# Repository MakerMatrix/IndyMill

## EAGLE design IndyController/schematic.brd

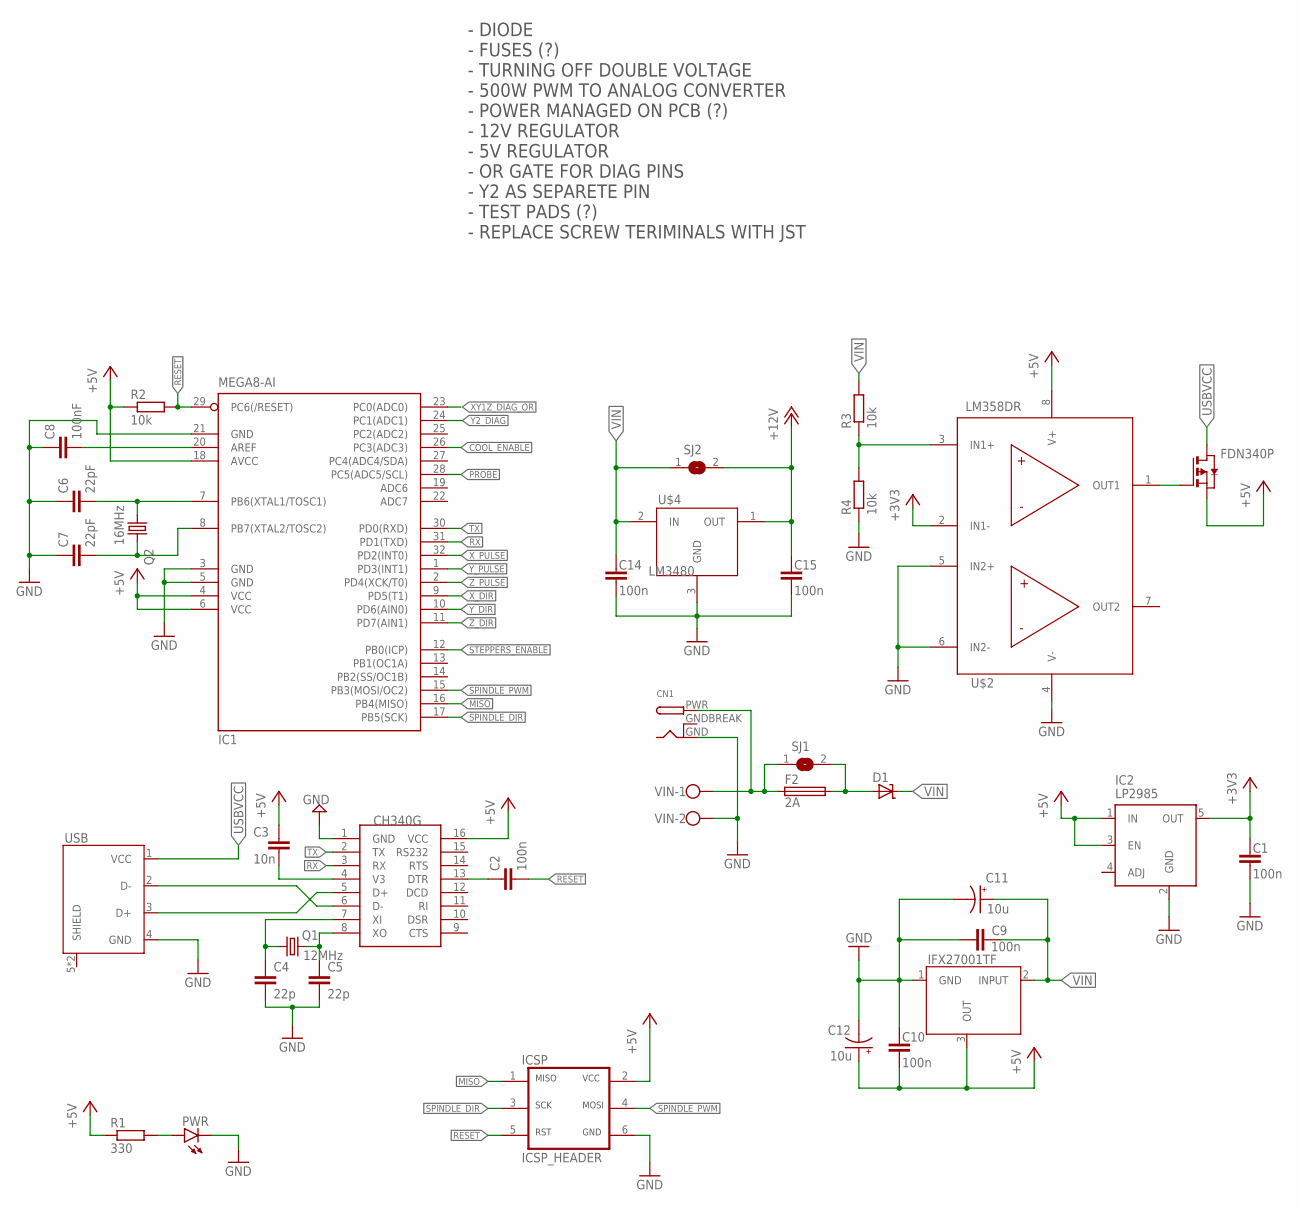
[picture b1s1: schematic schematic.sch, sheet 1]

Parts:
C1, C2, C9, C10, C14, C15: 100n; C0603
C3: 10n; C0603
C4, C5: 22p; C0603
C6, C7: 22pF; C0603
C8: 100nF; C0603
C11, C12: 10u; E5-5
CN1: DCBARRELPTH; DCJACK_2MM_PTH
D1: SD-SMA; SMA
F2: 2A; GSH15
FDN340P: FDN340PSOT23; SOT95P240X110-3N
IC1: MEGA8-AI; TQFP32-08
IC2: LP2985; SOT23-5
IFX27001TF: IFX27001TFV50TO252; TO228P998X230-3N
PWR: LEDCHIPLED_0805; CHIPLED_0805
Q1: 12MHz; 5.0X3.2_2
Q2: 16MHz; 5.0X3.2_2
R1: 330; R0603
R2, R3, R4: 10k; R0603
SJ1: SJW
SJ2: SJ
U$1: CH340G; SOIC16
U$2: LM358; SOIC127P599X175-8N
U$4: LM3480; SOT95P247X112-3N
U$6: ICSP_HEADER
USB: U-USBBR04P-F000
VIN: W237-102

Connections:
+3V3: C1.2, IC2.5 (OUT), U$2.2 (IN1-)
+5V: C3.1, C10.1, C12.+, FDN340P.2 (S), IC1.4 (VCC), IC1.6 (VCC), IC1.18 (AVCC), IC2.1 (IN), IC2.3 (EN), IFX27001TF.3 (OUT), R1.1, R2.1, U$1.16 (VCC), U$2.8 (V+), U$6.2 (VCC); also elsewhere on the board
+12V: C15.2, SJ2.2, U$4.1 (OUT); also elsewhere on the board
COOL_ENABLE: IC1.26 (PC3(ADC3)); also elsewhere on the board
GND: C1.1, C4.2, C5.2, C6.1, C7.1, C8.1, C9.1, C10.2, C11.-, C12.-, C14.1, C15.1, CN1.GND, IC1.3 (GND), IC1.5 (GND), IC1.21 (GND), IC2.2 (GND), IFX27001TF.1 (GND), PWR.C, R4.1, U$1.1 (GND), U$2.4 (V-), U$2.5 (IN2+), U$2.6 (IN2-), U$4.3 (GND), U$6.6 (GND), USB.4 (GND), VIN.2; also elsewhere on the board
GNDBREAK: CN1.GNDBREAK
MISO: IC1.16 (PB4(MISO)), U$6.1 (MISO)
unnamed: C3.2, U$1.4 (V3)
unnamed: C2.1, U$1.13 (DTR)
unnamed: C5.1, Q1.2, U$1.8 (XO)
unnamed: C4.1, Q1.1, U$1.7 (XI)
unnamed: U$1.6 (D-), USB.2 (D-)
unnamed: PWR.A, R1.2
unnamed: C6.2, IC1.7 (PB6(XTAL1/TOSC1)), Q2.1
unnamed: C7.2, IC1.8 (PB7(XTAL2/TOSC2)), Q2.2
unnamed: C8.2, IC1.20 (AREF)
unnamed: U$1.5 (D+), USB.3 (D+)
unnamed: FDN340P.1 (G), U$2.1 (OUT1)
unnamed: CN1.PWR, F2.1, SJ1.1, VIN.1
unnamed: R3.1, R4.2, U$2.3 (IN1+)
unnamed: D1.A, F2.2, SJ1.2
PROBE: IC1.28 (PC5(ADC5/SCL)); also elsewhere on the board
RESET: C2.2, IC1.29 (PC6(/RESET)), R2.2, U$6.5 (RST)
RX: IC1.31 (PD1(TXD)), U$1.3 (RX)
SPINDLE_DIR: IC1.17 (PB5(SCK)), U$6.3 (SCK); also elsewhere on the board
SPINDLE_PWM: IC1.15 (PB3(MOSI/OC2)), U$6.4 (MOSI); also elsewhere on the board
STEPPERS_ENABLE: IC1.12 (PB0(ICP)); also elsewhere on the board
TX: IC1.30 (PD0(RXD)), U$1.2 (TX)
USBVCC: FDN340P.3 (D), USB.1 (VCC)
VIN: C9.2, C11.+, C14.2, D1.C, IFX27001TF.2 (INPUT), R3.2, SJ2.1, U$4.2 (IN); also elsewhere on the board
XY1Z_DIAG_OR: IC1.23 (PC0(ADC0)); also elsewhere on the board
X_DIR: IC1.9 (PD5(T1)); also elsewhere on the board
X_PULSE: IC1.32 (PD2(INT0)); also elsewhere on the board
Y2_DIAG: IC1.24 (PC1(ADC1)); also elsewhere on the board
Y_DIR: IC1.10 (PD6(AIN0)); also elsewhere on the board
Y_PULSE: IC1.1 (PD3(INT1)); also elsewhere on the board
Z_DIR: IC1.11 (PD7(AIN1)); also elsewhere on the board
Z_PULSE: IC1.2 (PD4(XCK/T0)); also elsewhere on the board

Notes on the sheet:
- DIODE - FUSES (?) - TURNING OFF DOUBLE VOLTAGE - 500W PWM TO ANALOG CONVERTER - POWER MANAGED ON PCB (?) - 12V REGULATOR - 5V REGULATOR - OR GATE FOR DIAG PINS - Y2 AS SEPARETE PIN - TEST PADS (?) - REPLACE SCREW TERIMINALS WITH JST

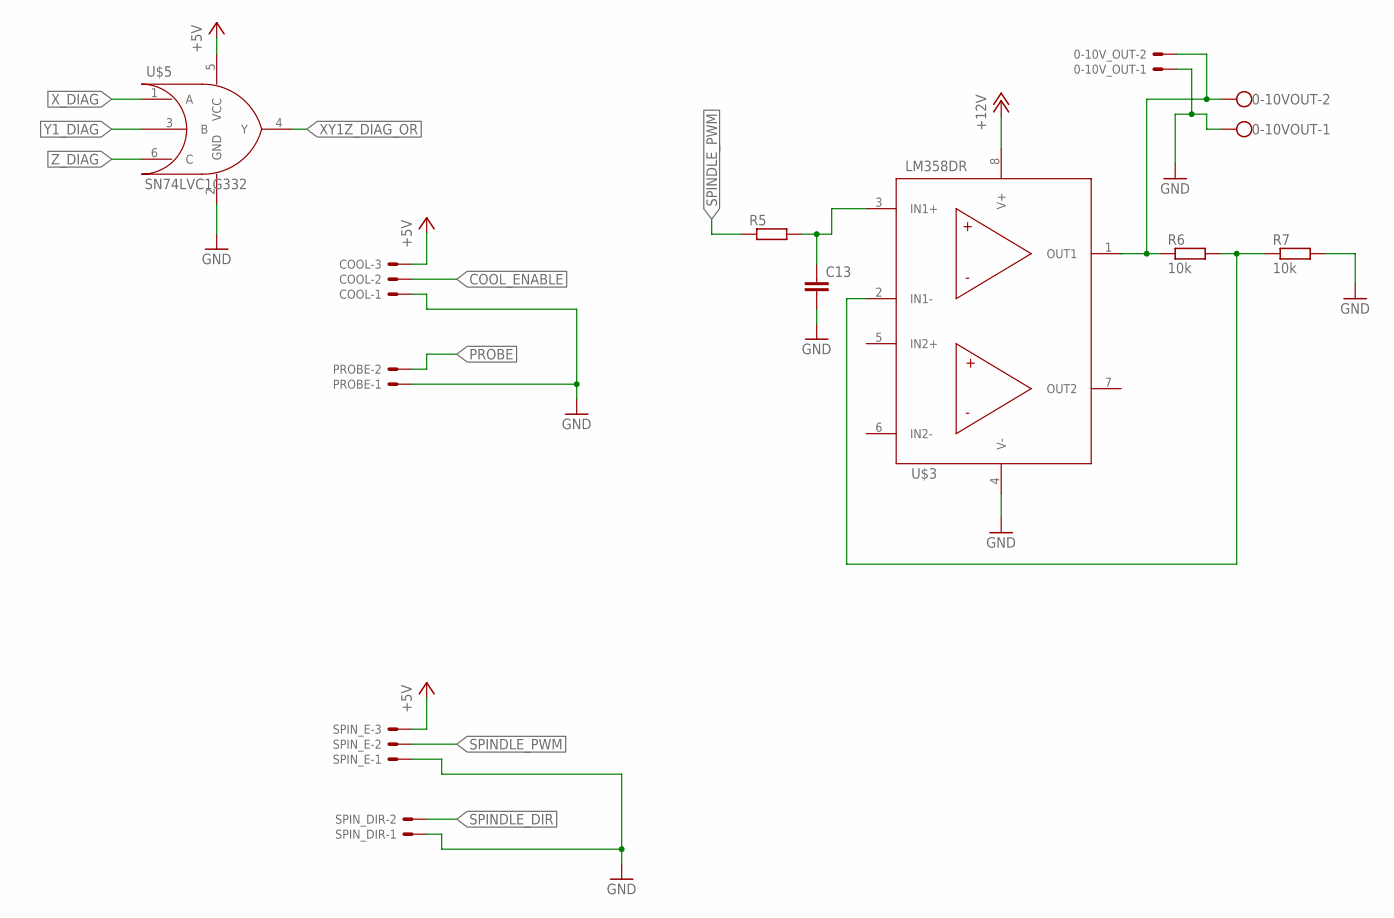
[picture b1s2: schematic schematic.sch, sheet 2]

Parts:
0-10VOUT: W237-102
0-10V_OUT: JST-XH-02-PIN-LONG-PAD; JST-XH-02-PACKAGE-LONG-PAD
C13: C-EUC0603; C0603
COOL: JST-XH-03-PIN-LONG-PAD; JST-XH-03-PACKAGE-LONG-PAD
PROBE: JST-XH-02-PIN-LONG-PAD; JST-XH-02-PACKAGE-LONG-PAD
R5: R-EU_R0603; R0603
R6, R7: 10k; R0603
SPIN_DIR: JST-XH-02-PIN-LONG-PAD; JST-XH-02-PACKAGE-LONG-PAD
SPIN_E: JST-XH-03-PIN-LONG-PAD; JST-XH-03-PACKAGE-LONG-PAD
U$3: LM358; SOIC127P599X175-8N
U$5: SN74LVC1G332; SOT95P280X110-6N

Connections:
+5V: COOL.3, SPIN_E.3, U$5.5 (VCC); also elsewhere on the board
+12V: U$3.8 (V+); also elsewhere on the board
COOL_ENABLE: COOL.2; also elsewhere on the board
GND: 0-10VOUT.1, 0-10V_OUT.1, C13.2, COOL.1, PROBE.1, R7.2, SPIN_DIR.1, SPIN_E.1, U$3.4 (V-), U$5.2 (GND); also elsewhere on the board
unnamed: C13.1, R5.2, U$3.3 (IN1+)
unnamed: R6.2, R7.1, U$3.2 (IN1-)
unnamed: 0-10VOUT.2, 0-10V_OUT.2, R6.1, U$3.1 (OUT1)
PROBE: PROBE.2; also elsewhere on the board
SPINDLE_DIR: SPIN_DIR.2; also elsewhere on the board
SPINDLE_PWM: R5.1, SPIN_E.2; also elsewhere on the board
XY1Z_DIAG_OR: U$5.4 (Y); also elsewhere on the board
X_DIAG: U$5.1 (A); also elsewhere on the board
Y1_DIAG: U$5.3 (B); also elsewhere on the board
Z_DIAG: U$5.6 (C); also elsewhere on the board

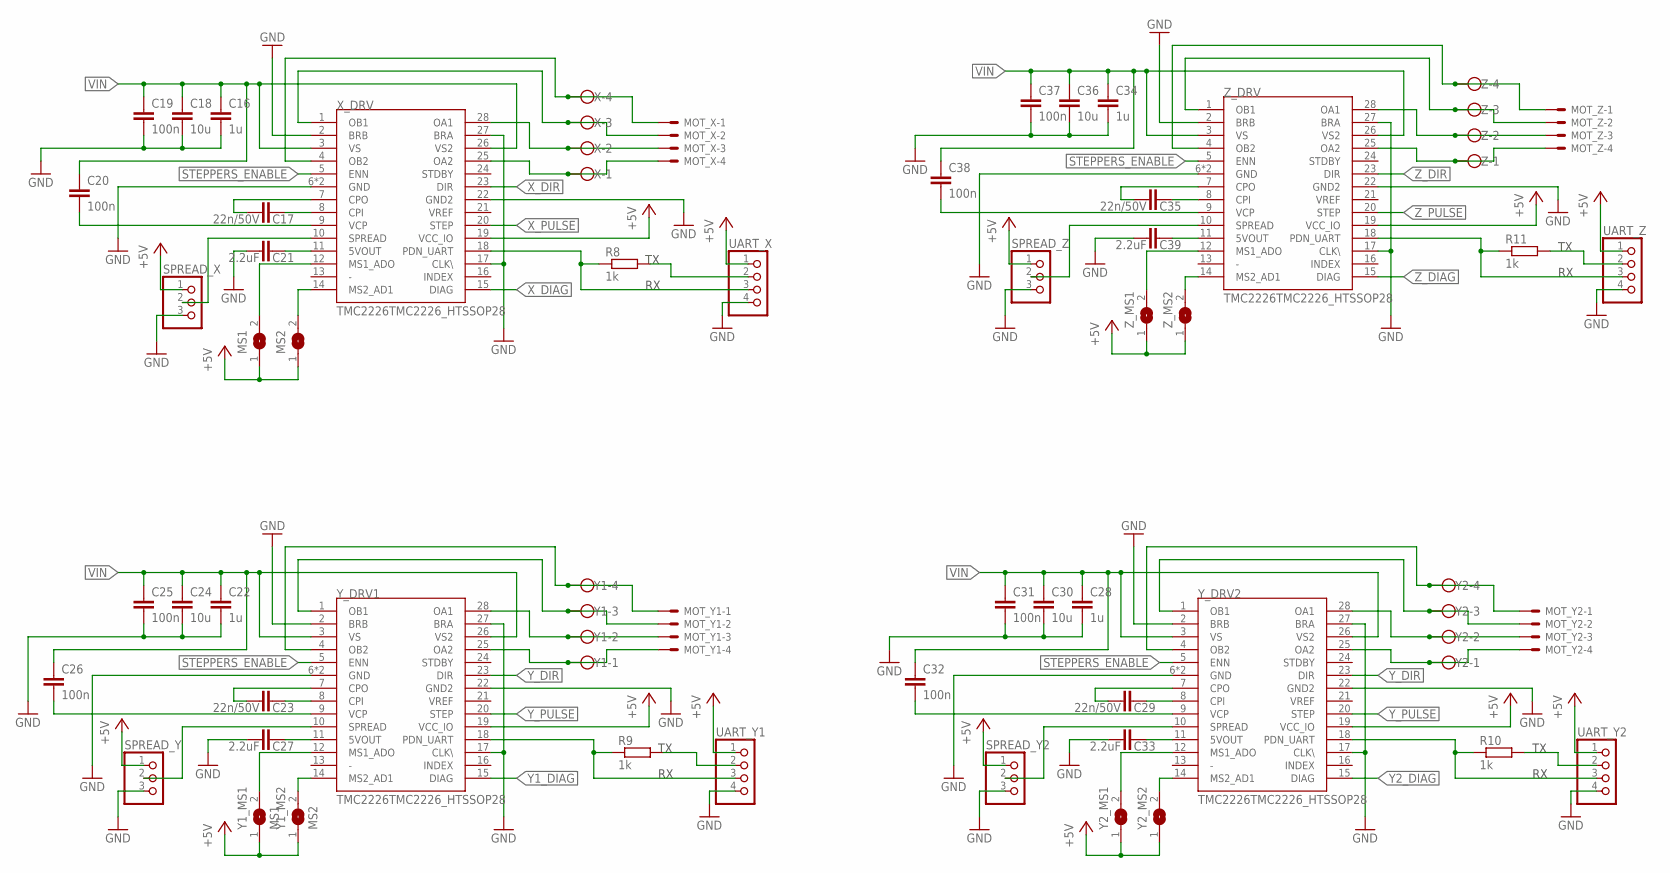
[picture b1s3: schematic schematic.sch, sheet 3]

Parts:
C16, C22, C28, C34: 1u; C0603
C17, C23, C29, C35: 22n/50V; C0603
C18, C24, C30, C36: 10u; C0603
C19, C20, C25, C26, C31, C32, C37, C38: 100n; C0603
C21, C27, C33, C39: 2.2uF; C0603
MOT_X: JST-XH-04-PIN-LONG-PAD; JST-XH-04-PACKAGE-LONG-PAD
MOT_Y1, MOT_Y2: JST-XH-04-PIN-LONG-PAD; JST-XH-04-PACKAGE-LONG-PAD
MOT_Z: JST-XH-04-PIN-LONG-PAD; JST-XH-04-PACKAGE-LONG-PAD
MS1, MS2: SJ
R8, R9, R10, R11: 1k; R0603
SPREAD_X: PINHD-1X3; 1X03
SPREAD_Y, SPREAD_Y2: PINHD-1X3; 1X03
SPREAD_Z: PINHD-1X3; 1X03
UART_X: PINHD-1X4; 1X04
UART_Y1, UART_Y2: PINHD-1X4; 1X04
UART_Z: PINHD-1X4; 1X04
X: W237-4
X_DRV: TMC2226TMC2226_HTSSOP28; SOP65P640X120-29T275X620N
Y1, Y2: W237-4
Y1_MS1: MS1; SJ
Y1_MS2: MS2; SJ
Y2_MS1, Y2_MS2: SJ
Y_DRV1, Y_DRV2: TMC2226TMC2226_HTSSOP28; SOP65P640X120-29T275X620N
Z: W237-4
Z_DRV: TMC2226TMC2226_HTSSOP28; SOP65P640X120-29T275X620N
Z_MS1, Z_MS2: SJ

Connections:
+5V: MS1.1, MS2.1, SPREAD_X.1, SPREAD_Y.1, SPREAD_Y2.1, SPREAD_Z.1, UART_X.1, UART_Y1.1, UART_Y2.1, UART_Z.1, X_DRV.19 (VCC_IO), Y1_MS1.1, Y1_MS2.1, Y2_MS1.1, Y2_MS2.1, Y_DRV1.19 (VCC_IO), Y_DRV2.19 (VCC_IO), Z_DRV.19 (VCC_IO), Z_MS1.1, Z_MS2.1; also elsewhere on the board
GND: C16.2, C18.2, C19.2, C21.1, C22.2, C24.2, C25.2, C27.1, C28.2, C30.2, C31.2, C33.1, C34.2, C36.2, C37.2, C39.1, SPREAD_X.3, SPREAD_Y.3, SPREAD_Y2.3, SPREAD_Z.3, UART_X.4, UART_Y1.4, UART_Y2.4, UART_Z.4, X_DRV.2 (BRB), X_DRV.6 (GND), X_DRV.17 (CLK\), X_DRV.22 (GND2), X_DRV.27 (BRA), X_DRV.29 (GND), Y_DRV1.2 (BRB), Y_DRV1.6 (GND), Y_DRV1.17 (CLK\), Y_DRV1.22 (GND2), Y_DRV1.27 (BRA), Y_DRV1.29 (GND), Y_DRV2.2 (BRB), Y_DRV2.6 (GND), Y_DRV2.17 (CLK\), Y_DRV2.22 (GND2), Y_DRV2.27 (BRA), Y_DRV2.29 (GND), Z_DRV.2 (BRB), Z_DRV.6 (GND), Z_DRV.17 (CLK\), Z_DRV.22 (GND2), Z_DRV.27 (BRA), Z_DRV.29 (GND); also elsewhere on the board
unnamed: C17.2, X_DRV.8 (CPI)
unnamed: C17.1, X_DRV.7 (CPO)
unnamed: MOT_X.1, X.4, X_DRV.4 (OB2)
unnamed: MOT_X.2, X.3, X_DRV.1 (OB1)
unnamed: MOT_X.3, X.2, X_DRV.28 (OA1)
unnamed: MOT_X.4, X.1, X_DRV.25 (OA2)
unnamed: SPREAD_X.2, X_DRV.10 (SPREAD)
unnamed: C20.2, X_DRV.9 (VCP)
unnamed: C21.2, X_DRV.11 (5VOUT)
unnamed: R8.1, UART_X.3, X_DRV.18 (PDN_UART)
unnamed: MS1.2, X_DRV.12 (MS1_ADO)
unnamed: MS2.2, X_DRV.14 (MS2_AD1)
unnamed: R8.2, UART_X.2
unnamed: C23.2, Y_DRV1.8 (CPI)
unnamed: C23.1, Y_DRV1.7 (CPO)
unnamed: MOT_Y1.1, Y1.4, Y_DRV1.4 (OB2)
unnamed: MOT_Y1.2, Y1.3, Y_DRV1.1 (OB1)
unnamed: MOT_Y1.3, Y1.2, Y_DRV1.28 (OA1)
unnamed: MOT_Y1.4, Y1.1, Y_DRV1.25 (OA2)
unnamed: C26.2, Y_DRV1.9 (VCP)
unnamed: SPREAD_Y.2, Y_DRV1.10 (SPREAD)
unnamed: C27.2, Y_DRV1.11 (5VOUT)
unnamed: Y1_MS1.2, Y_DRV1.12 (MS1_ADO)
unnamed: Y1_MS2.2, Y_DRV1.14 (MS2_AD1)
unnamed: R9.1, UART_Y1.3, Y_DRV1.18 (PDN_UART)
unnamed: R9.2, UART_Y1.2
unnamed: C29.2, Y_DRV2.8 (CPI)
unnamed: C29.1, Y_DRV2.7 (CPO)
unnamed: MOT_Y2.1, Y2.4, Y_DRV2.4 (OB2)
unnamed: MOT_Y2.2, Y2.3, Y_DRV2.1 (OB1)
unnamed: MOT_Y2.3, Y2.2, Y_DRV2.28 (OA1)
unnamed: MOT_Y2.4, Y2.1, Y_DRV2.25 (OA2)
unnamed: C32.2, Y_DRV2.9 (VCP)
unnamed: SPREAD_Y2.2, Y_DRV2.10 (SPREAD)
unnamed: C33.2, Y_DRV2.11 (5VOUT)
unnamed: Y2_MS1.2, Y_DRV2.12 (MS1_ADO)
unnamed: Y2_MS2.2, Y_DRV2.14 (MS2_AD1)
unnamed: R10.1, UART_Y2.3, Y_DRV2.18 (PDN_UART)
unnamed: R10.2, UART_Y2.2
unnamed: C35.2, Z_DRV.8 (CPI)
unnamed: C35.1, Z_DRV.7 (CPO)
unnamed: MOT_Z.1, Z.4, Z_DRV.4 (OB2)
unnamed: MOT_Z.2, Z.3, Z_DRV.1 (OB1)
unnamed: MOT_Z.3, Z.2, Z_DRV.28 (OA1)
unnamed: MOT_Z.4, Z.1, Z_DRV.25 (OA2)
unnamed: C38.2, Z_DRV.9 (VCP)
unnamed: SPREAD_Z.2, Z_DRV.10 (SPREAD)
unnamed: C39.2, Z_DRV.11 (5VOUT)
unnamed: Z_DRV.12 (MS1_ADO), Z_MS1.2
unnamed: Z_DRV.14 (MS2_AD1), Z_MS2.2
unnamed: R11.1, UART_Z.3, Z_DRV.18 (PDN_UART)
unnamed: R11.2, UART_Z.2
STEPPERS_ENABLE: X_DRV.5 (ENN), Y_DRV1.5 (ENN), Y_DRV2.5 (ENN), Z_DRV.5 (ENN); also elsewhere on the board
VIN: C16.1, C18.1, C19.1, C20.1, C22.1, C24.1, C25.1, C26.1, C28.1, C30.1, C31.1, C32.1, C34.1, C36.1, C37.1, C38.1, X_DRV.3 (VS), X_DRV.26 (VS2), Y_DRV1.3 (VS), Y_DRV1.26 (VS2), Y_DRV2.3 (VS), Y_DRV2.26 (VS2), Z_DRV.3 (VS), Z_DRV.26 (VS2); also elsewhere on the board
X_DIAG: X_DRV.15 (DIAG); also elsewhere on the board
X_DIR: X_DRV.23 (DIR); also elsewhere on the board
X_PULSE: X_DRV.20 (STEP); also elsewhere on the board
Y1_DIAG: Y_DRV1.15 (DIAG); also elsewhere on the board
Y2_DIAG: Y_DRV2.15 (DIAG); also elsewhere on the board
Y_DIR: Y_DRV1.23 (DIR), Y_DRV2.23 (DIR); also elsewhere on the board
Y_PULSE: Y_DRV1.20 (STEP), Y_DRV2.20 (STEP); also elsewhere on the board
Z_DIAG: Z_DRV.15 (DIAG); also elsewhere on the board
Z_DIR: Z_DRV.23 (DIR); also elsewhere on the board
Z_PULSE: Z_DRV.20 (STEP); also elsewhere on the board

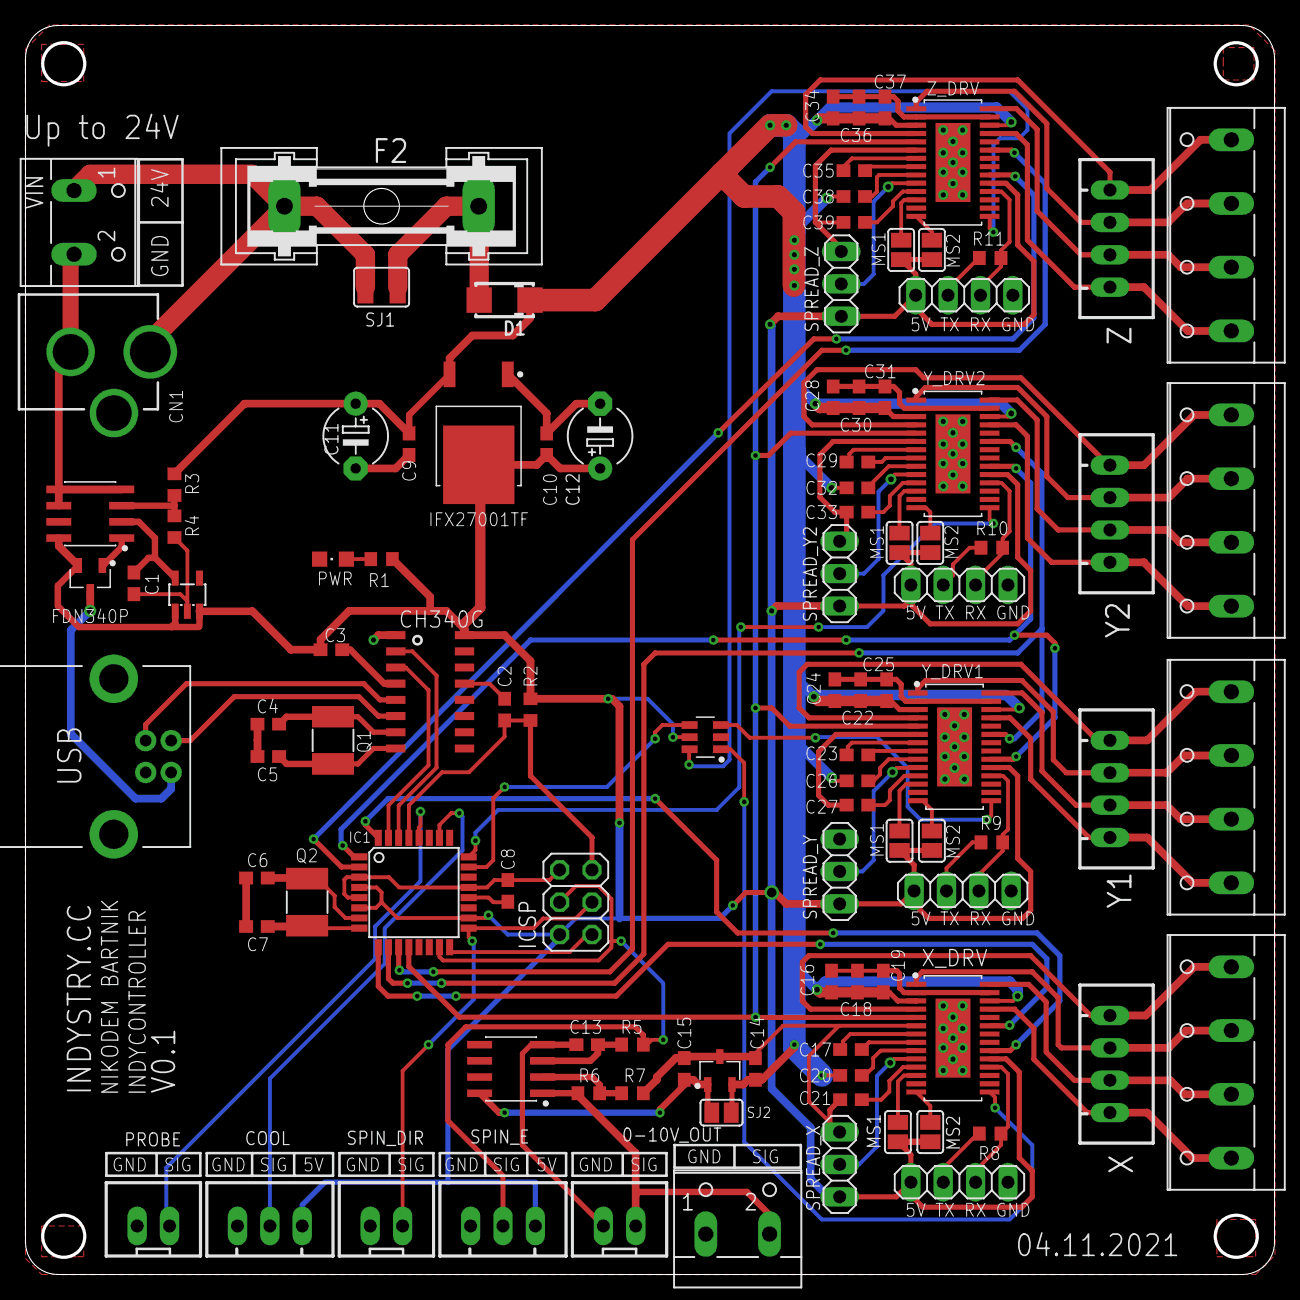
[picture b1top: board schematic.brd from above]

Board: 2 copper layers, 98.0 x 98.0 mm, 104 parts (0 on the bottom side), 95 nets.

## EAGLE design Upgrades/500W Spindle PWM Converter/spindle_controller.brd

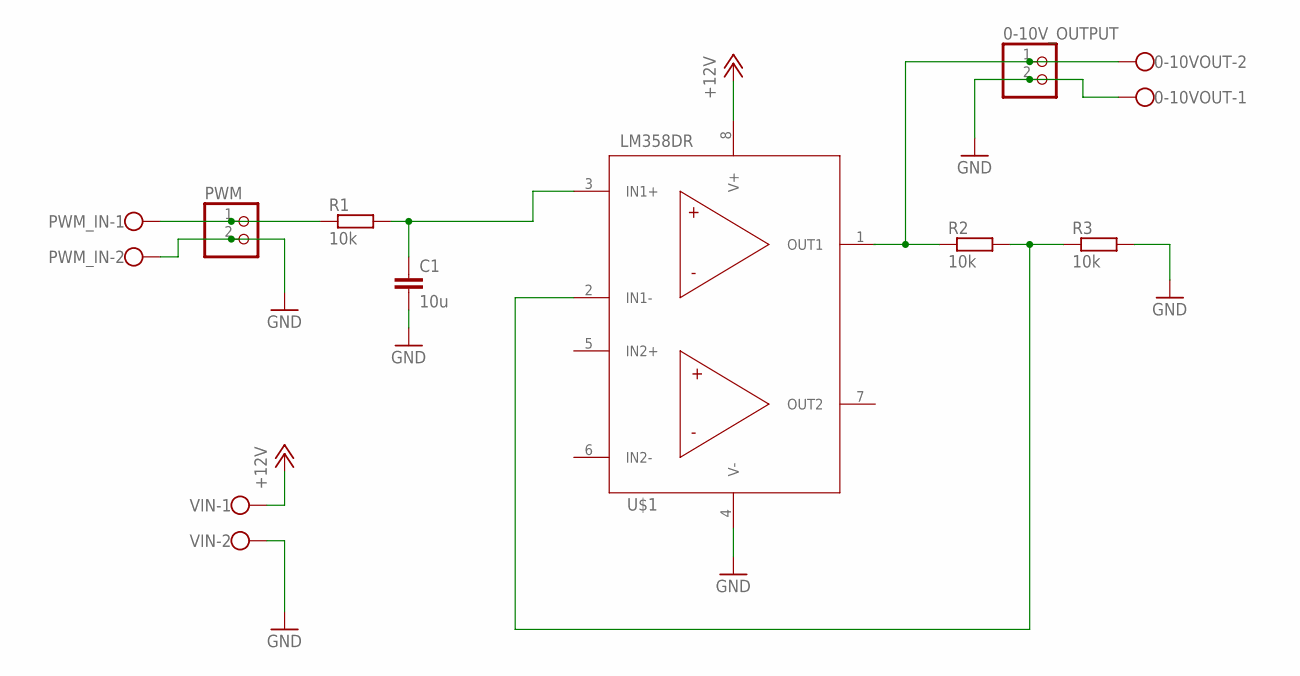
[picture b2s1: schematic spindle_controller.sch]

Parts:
0-10VOUT: W237-102
0-10V_OUTPUT: PINHD-1X2; 1X02
C1: 10u; C0603
PWM: PINHD-1X2; 1X02
PWM_IN: W237-102
R1, R2, R3: 10k; R0603
U$1: LM358DRLM358DR_SOIC8; SOIC127P599X175-8N
VIN: W237-102

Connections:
+12V: U$1.8 (V+), VIN.1
GND: 0-10VOUT.1, 0-10V_OUTPUT.2, C1.2, PWM.2, PWM_IN.2, R3.2, U$1.4 (V-), VIN.2
unnamed: PWM.1, PWM_IN.1, R1.1
unnamed: C1.1, R1.2, U$1.3 (IN1+)
unnamed: R2.2, R3.1, U$1.2 (IN1-)
unnamed: 0-10VOUT.2, 0-10V_OUTPUT.1, R2.1, U$1.1 (OUT1)

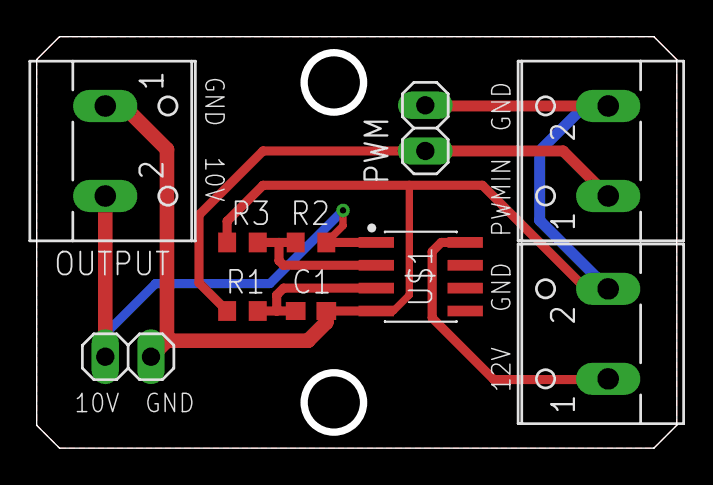
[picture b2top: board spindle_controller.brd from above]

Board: 2 copper layers, 35.6 x 22.9 mm, 10 parts (0 on the bottom side), 6 nets.

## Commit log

2021-09-04 Add IndyController schematic and board file (work in progress)
2021-09-05 Add 12V regulator, PCB layout
2021-09-07 PCB cleanup and missing values added to schematic
2021-10-04 Add TMC2226 to the schematic with datasheet, create changelog
2021-10-24 Redesign spindle light
    Spindle light with bigger hole (30.5mm) to get it working with 1.5kW spindle too.
2021-10-30 Get rid of some components, connect TMC drivers almost completely
2021-10-31 Add some connections and parts to the list
2021-11-01 Ports redesign, final dimensions, most connections ready
2021-11-01 JST connectors, polygons, final dimensions, screw holes
2021-11-02 Cleanup + or gate datasheet
2021-11-04 Add OR gate, thicker traces
2021-11-05 Final cleanup for V0.1!
2021-11-18 BOM update

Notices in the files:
parts and their libraries:
crystal-geyer_V1_0: Copyright: Geyer-Electronic
